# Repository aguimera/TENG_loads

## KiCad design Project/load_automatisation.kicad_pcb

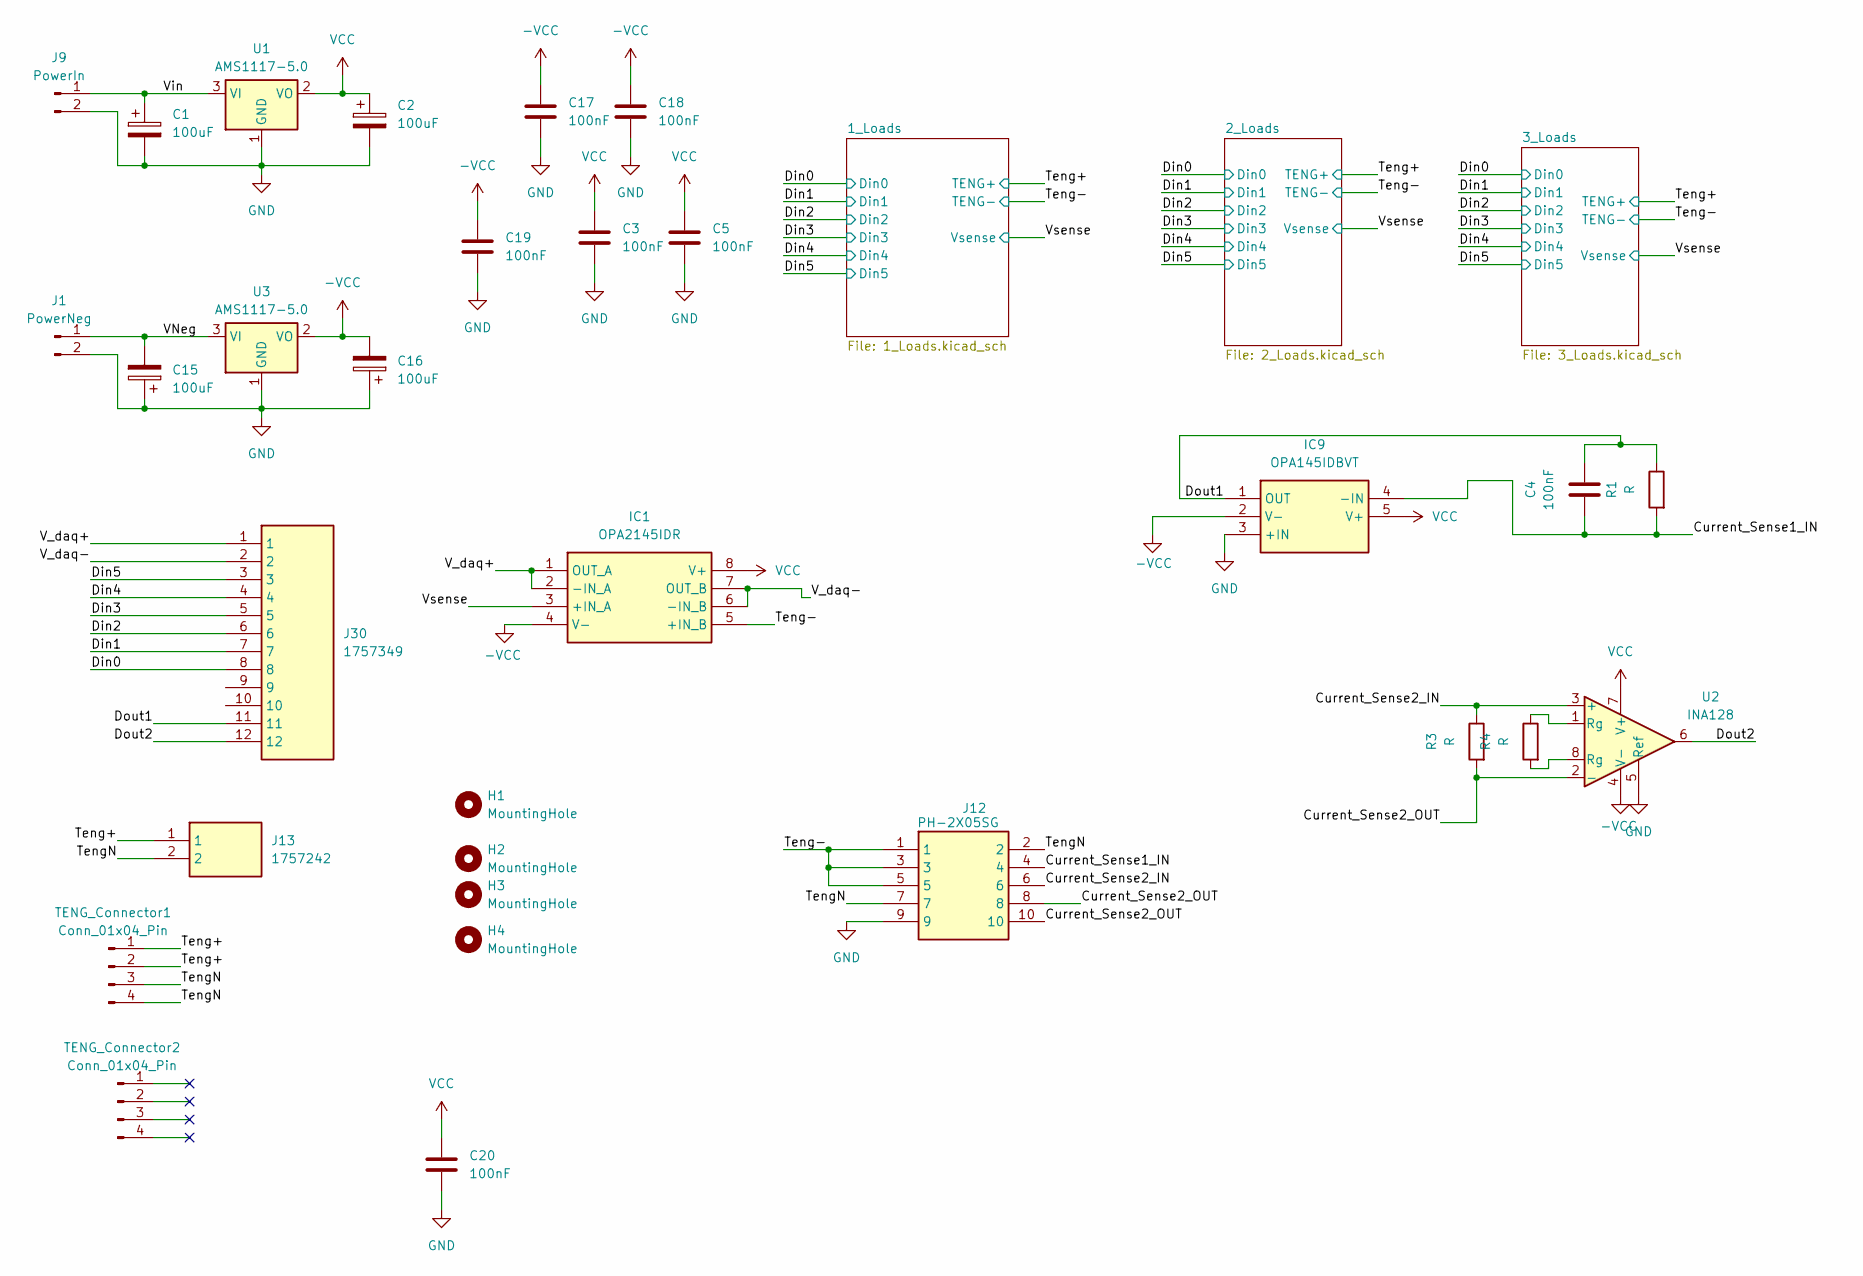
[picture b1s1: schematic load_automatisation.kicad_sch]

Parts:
C1, C2, C15, C16: 100uF; CP_Radial_D8.0mm_P3.80mm
C3, C4, C5, C17, C18, C19, C20: 100nF; C_0805_2012Metric
H1, H2, H3, H4: MountingHole; MountingHole_5.3mm_M5
IC1: OPA2145IDR; SOIC127P600X175-8N; Manufacturer_Part_Number OPA2145IDR; Mouser Part Number 595-OPA2145IDR
IC9: OPA145IDBVT; SOT95P280X145-5N; Manufacturer_Part_Number OPA145IDBVT; Mouser Part Number 595-OPA145IDBVT
J1: PowerNeg; PinHeader_1x02_P2.54mm_Vertical
J9: PowerIn; PinHeader_1x02_P2.54mm_Vertical
J12: PH-2X05SG; HDRV10W66P254_2X5_1270X500X895P; Manufacturer_Part_Number PH-2X05SG
J13: 1757242; Manufacturer_Part_Number 1757242; Mouser Part Number 651-1757242
J30: 1757349; SHDRRA12W103P0X508_1X12_6296X1200X875P; Manufacturer_Part_Number 1757349; Mouser Part Number 651-1757349
R1, R3, R4: R; R_0805_2012Metric
TENG_Connector1, TENG_Connector2: Conn_01x04_Pin; PinHeader_1x04_P2.54mm_Vertical
U1, U3: AMS1117-5.0; SOT-223-3_TabPin2
U2: INA128; SOIC-8_3.9x4.9mm_P1.27mm

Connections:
-VCC: C16.2, C17.1, C18.1, C19.1, IC1.4 (V-), IC9.2 (V-), U2.4 (V-), U3.2 (VO)
/Current_Sense1_IN: C4.1, IC9.4 (-IN), J12.4, R1.2
/Current_Sense2_IN: J12.6, R3.1, U2.3 (+)
/Current_Sense2_OUT: J12.8, J12.10, R3.2, U2.2 (-)
/Din0: J30.8; also elsewhere on the board
/Din1: J30.7; also elsewhere on the board
/Din2: J30.6; also elsewhere on the board
/Din3: J30.5; also elsewhere on the board
/Din4: J30.4; also elsewhere on the board
/Din5: J30.3; also elsewhere on the board
/Dout1: C4.2, IC9.1 (OUT), J30.11, R1.1
/Dout2: J30.12, U2.6
/Teng+: J13.1, TENG_Connector1.1, TENG_Connector1.2; also elsewhere on the board
/Teng-: IC1.5 (+IN_B), J12.1, J12.3, J12.5; also elsewhere on the board
/TengN: J12.2, J12.7, J13.2, TENG_Connector1.3, TENG_Connector1.4
/VNeg: C15.2, J1.1, U3.3 (VI)
/V_daq+: IC1.1 (OUT_A), IC1.2 (-IN_A), J30.1
/V_daq-: IC1.6 (-IN_B), IC1.7 (OUT_B), J30.2
/Vin: C1.1, J9.1, U1.3 (VI)
/Vsense: IC1.3 (+IN_A); also elsewhere on the board
GND: C1.2, C2.2, C3.2, C5.2, C15.1, C16.1, C17.2, C18.2, C19.2, C20.2, IC9.3 (+IN), J1.2, J9.2, J12.9, U1.1 (GND), U2.5 (Ref), U3.1 (GND); also elsewhere on the board
unnamed: R4.1, U2.1 (Rg)
unnamed: R4.2, U2.8 (Rg)
VCC: C2.1, C3.1, C5.1, C20.1, IC1.8 (V+), IC9.5 (V+), U1.2 (VO), U2.7 (V+); also elsewhere on the board

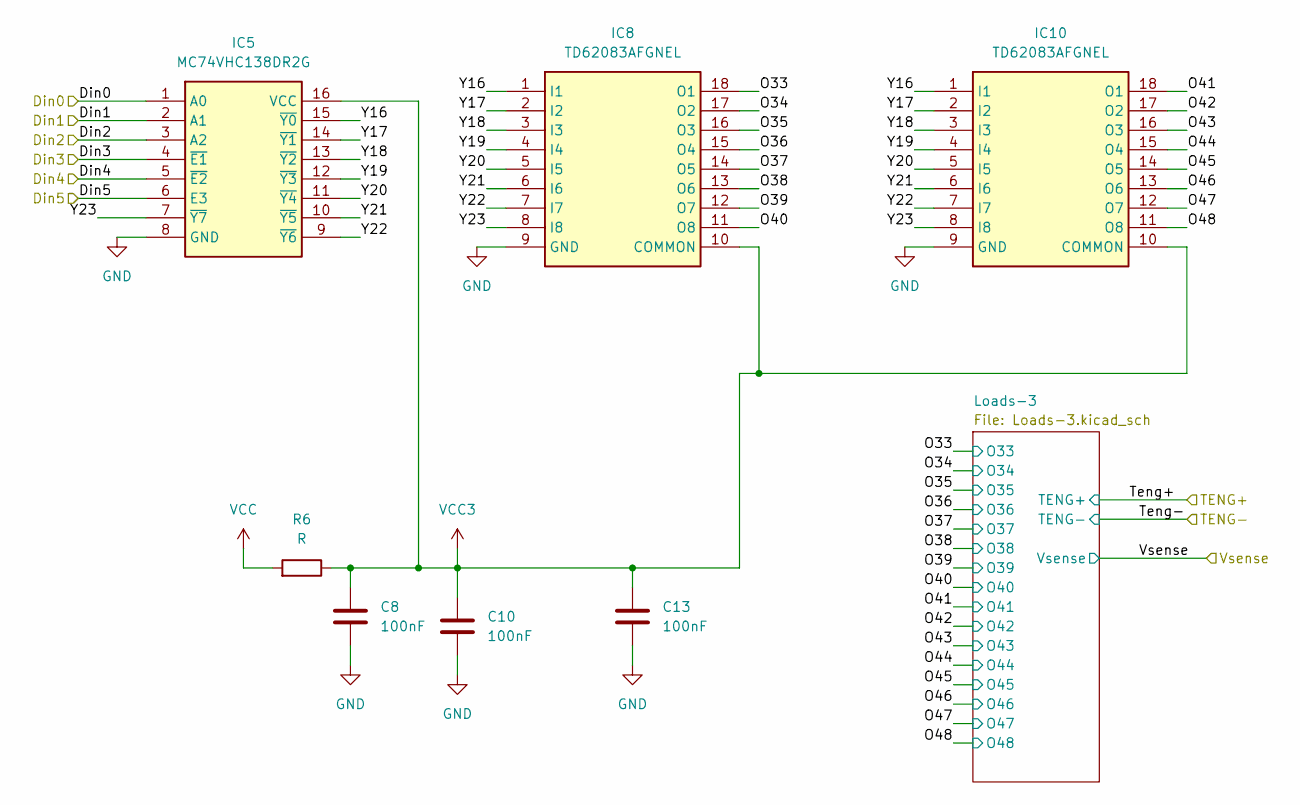
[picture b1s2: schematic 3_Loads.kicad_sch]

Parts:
C8, C10, C13: 100nF; C_0805_2012Metric
IC5: MC74VHC138DR2G; SOIC127P600X175-16N; Manufacturer_Part_Number MC74VHC138DR2G; Mouser Part Number 863-MC74VHC138DR2G
IC8, IC10: TD62083AFGNEL; SOIC127P1030X245-18N; Manufacturer_Part_Number TD62083AFGNEL; Mouser Part Number N/A
R6: R; R_0805_2012Metric

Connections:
/3_Loads/O33: IC8.18 (O1); also elsewhere on the board
/3_Loads/O34: IC8.17 (O2); also elsewhere on the board
/3_Loads/O35: IC8.16 (O3); also elsewhere on the board
/3_Loads/O36: IC8.15 (O4); also elsewhere on the board
/3_Loads/O37: IC8.14 (O5); also elsewhere on the board
/3_Loads/O38: IC8.13 (O6); also elsewhere on the board
/3_Loads/O39: IC8.12 (O7); also elsewhere on the board
/3_Loads/O40: IC8.11 (O8); also elsewhere on the board
/3_Loads/O41: IC10.18 (O1); also elsewhere on the board
/3_Loads/O42: IC10.17 (O2); also elsewhere on the board
/3_Loads/O43: IC10.16 (O3); also elsewhere on the board
/3_Loads/O44: IC10.15 (O4); also elsewhere on the board
/3_Loads/O45: IC10.14 (O5); also elsewhere on the board
/3_Loads/O46: IC10.13 (O6); also elsewhere on the board
/3_Loads/O47: IC10.12 (O7); also elsewhere on the board
/3_Loads/O48: IC10.11 (O8); also elsewhere on the board
/3_Loads/Y16: IC5.15 (~Y0), IC8.1 (I1), IC10.1 (I1)
/3_Loads/Y17: IC5.14 (~Y1), IC8.2 (I2), IC10.2 (I2)
/3_Loads/Y18: IC5.13 (~Y2), IC8.3 (I3), IC10.3 (I3)
/3_Loads/Y19: IC5.12 (~Y3), IC8.4 (I4), IC10.4 (I4)
/3_Loads/Y20: IC5.11 (~Y4), IC8.5 (I5), IC10.5 (I5)
/3_Loads/Y21: IC5.10 (~Y5), IC8.6 (I6), IC10.6 (I6)
/3_Loads/Y22: IC5.9 (~Y6), IC8.7 (I7), IC10.7 (I7)
/3_Loads/Y23: IC5.7 (~Y7), IC8.8 (I8), IC10.8 (I8)
/Din0: IC5.1 (A0); also elsewhere on the board
/Din1: IC5.2 (A1); also elsewhere on the board
/Din2: IC5.3 (A2); also elsewhere on the board
/Din3: IC5.4 (~E1); also elsewhere on the board
/Din4: IC5.5 (~E2); also elsewhere on the board
/Din5: IC5.6 (E3); also elsewhere on the board
GND: C8.2, C10.2, C13.2, IC5.8 (GND), IC8.9 (GND), IC10.9 (GND); also elsewhere on the board
VCC: R6.2; also elsewhere on the board
VCC3: C8.1, C10.1, C13.1, IC5.16 (VCC), IC8.10 (COMMON), IC10.10 (COMMON), R6.1

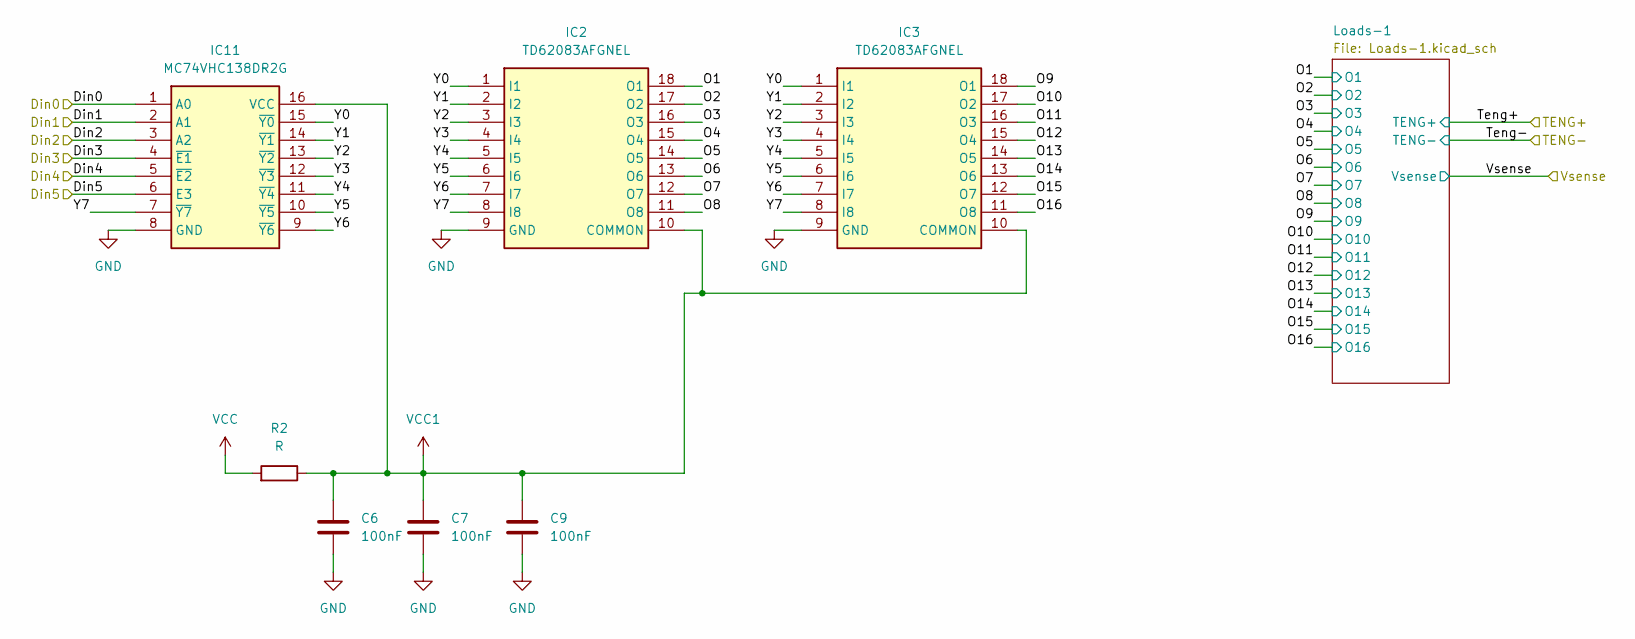
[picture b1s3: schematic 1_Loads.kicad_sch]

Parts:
C6, C7, C9: 100nF; C_0805_2012Metric
IC2, IC3: TD62083AFGNEL; SOIC127P1030X245-18N; Manufacturer_Part_Number TD62083AFGNEL; Mouser Part Number N/A
IC11: MC74VHC138DR2G; SOIC127P600X175-16N; Manufacturer_Part_Number MC74VHC138DR2G; Mouser Part Number 863-MC74VHC138DR2G
R2: R; R_0805_2012Metric

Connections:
/1_Loads/O1: IC2.18 (O1); also elsewhere on the board
/1_Loads/O2: IC2.17 (O2); also elsewhere on the board
/1_Loads/O3: IC2.16 (O3); also elsewhere on the board
/1_Loads/O4: IC2.15 (O4); also elsewhere on the board
/1_Loads/O5: IC2.14 (O5); also elsewhere on the board
/1_Loads/O6: IC2.13 (O6); also elsewhere on the board
/1_Loads/O7: IC2.12 (O7); also elsewhere on the board
/1_Loads/O8: IC2.11 (O8); also elsewhere on the board
/1_Loads/O9: IC3.18 (O1); also elsewhere on the board
/1_Loads/O10: IC3.17 (O2); also elsewhere on the board
/1_Loads/O11: IC3.16 (O3); also elsewhere on the board
/1_Loads/O12: IC3.15 (O4); also elsewhere on the board
/1_Loads/O13: IC3.14 (O5); also elsewhere on the board
/1_Loads/O14: IC3.13 (O6); also elsewhere on the board
/1_Loads/O15: IC3.12 (O7); also elsewhere on the board
/1_Loads/O16: IC3.11 (O8); also elsewhere on the board
/1_Loads/Y0: IC2.1 (I1), IC3.1 (I1), IC11.15 (~Y0)
/1_Loads/Y1: IC2.2 (I2), IC3.2 (I2), IC11.14 (~Y1)
/1_Loads/Y2: IC2.3 (I3), IC3.3 (I3), IC11.13 (~Y2)
/1_Loads/Y3: IC2.4 (I4), IC3.4 (I4), IC11.12 (~Y3)
/1_Loads/Y4: IC2.5 (I5), IC3.5 (I5), IC11.11 (~Y4)
/1_Loads/Y5: IC2.6 (I6), IC3.6 (I6), IC11.10 (~Y5)
/1_Loads/Y6: IC2.7 (I7), IC3.7 (I7), IC11.9 (~Y6)
/1_Loads/Y7: IC2.8 (I8), IC3.8 (I8), IC11.7 (~Y7)
/Din0: IC11.1 (A0); also elsewhere on the board
/Din1: IC11.2 (A1); also elsewhere on the board
/Din2: IC11.3 (A2); also elsewhere on the board
/Din3: IC11.4 (~E1); also elsewhere on the board
/Din4: IC11.5 (~E2); also elsewhere on the board
/Din5: IC11.6 (E3); also elsewhere on the board
GND: C6.2, C7.2, C9.2, IC2.9 (GND), IC3.9 (GND), IC11.8 (GND); also elsewhere on the board
VCC: R2.2; also elsewhere on the board
VCC1: C6.1, C7.1, C9.1, IC2.10 (COMMON), IC3.10 (COMMON), IC11.16 (VCC), R2.1

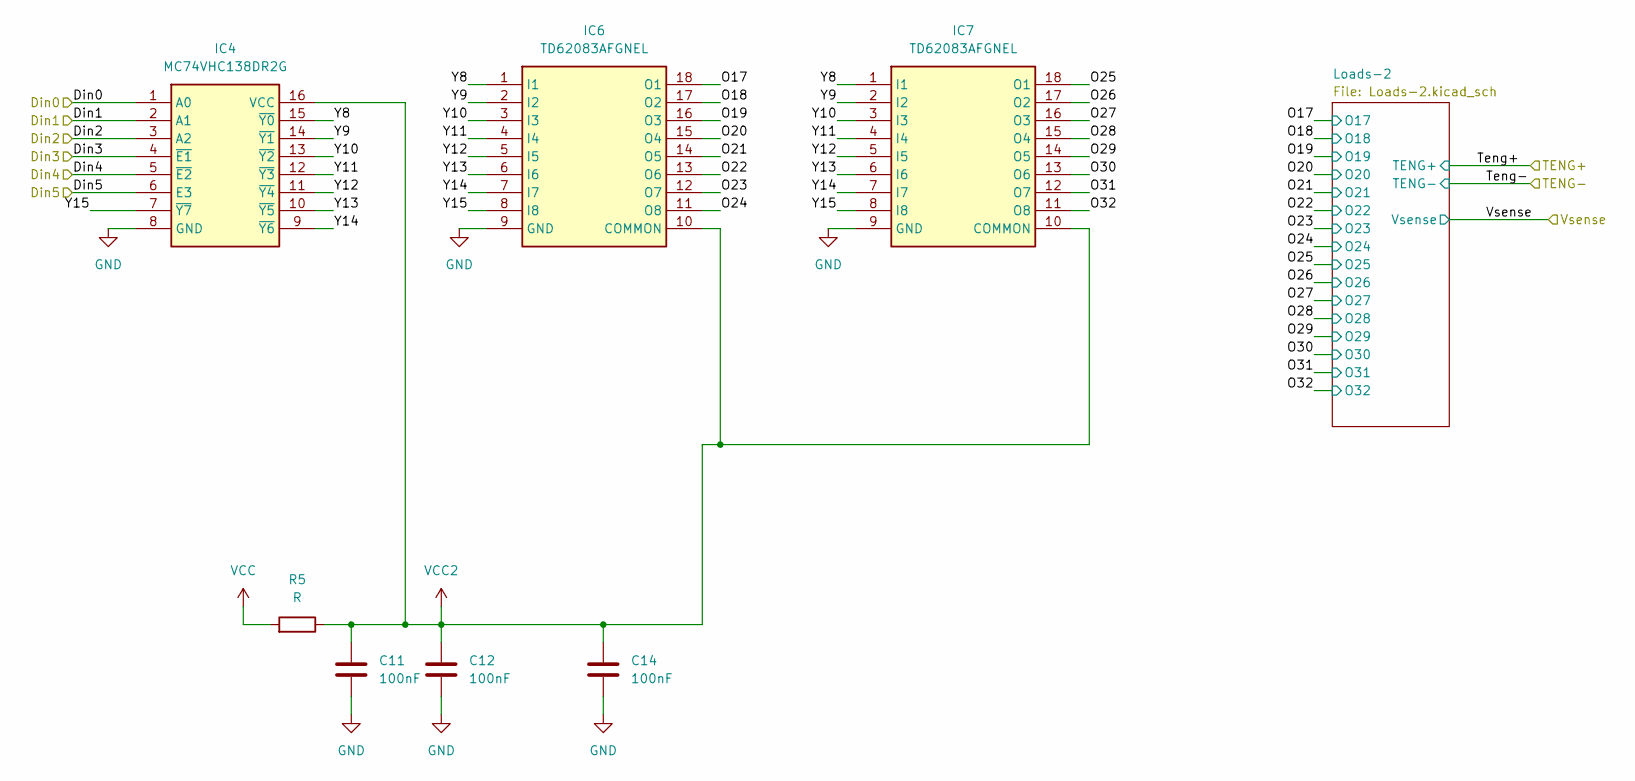
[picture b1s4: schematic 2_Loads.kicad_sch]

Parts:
C11, C12, C14: 100nF; C_0805_2012Metric
IC4: MC74VHC138DR2G; SOIC127P600X175-16N; Manufacturer_Part_Number MC74VHC138DR2G; Mouser Part Number 863-MC74VHC138DR2G
IC6, IC7: TD62083AFGNEL; SOIC127P1030X245-18N; Manufacturer_Part_Number TD62083AFGNEL; Mouser Part Number N/A
R5: R; R_0805_2012Metric

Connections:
/2_Loads/O17: IC6.18 (O1); also elsewhere on the board
/2_Loads/O18: IC6.17 (O2); also elsewhere on the board
/2_Loads/O19: IC6.16 (O3); also elsewhere on the board
/2_Loads/O20: IC6.15 (O4); also elsewhere on the board
/2_Loads/O21: IC6.14 (O5); also elsewhere on the board
/2_Loads/O22: IC6.13 (O6); also elsewhere on the board
/2_Loads/O23: IC6.12 (O7); also elsewhere on the board
/2_Loads/O24: IC6.11 (O8); also elsewhere on the board
/2_Loads/O25: IC7.18 (O1); also elsewhere on the board
/2_Loads/O26: IC7.17 (O2); also elsewhere on the board
/2_Loads/O27: IC7.16 (O3); also elsewhere on the board
/2_Loads/O28: IC7.15 (O4); also elsewhere on the board
/2_Loads/O29: IC7.14 (O5); also elsewhere on the board
/2_Loads/O30: IC7.13 (O6); also elsewhere on the board
/2_Loads/O31: IC7.12 (O7); also elsewhere on the board
/2_Loads/O32: IC7.11 (O8); also elsewhere on the board
/2_Loads/Y8: IC4.15 (~Y0), IC6.1 (I1), IC7.1 (I1)
/2_Loads/Y9: IC4.14 (~Y1), IC6.2 (I2), IC7.2 (I2)
/2_Loads/Y10: IC4.13 (~Y2), IC6.3 (I3), IC7.3 (I3)
/2_Loads/Y11: IC4.12 (~Y3), IC6.4 (I4), IC7.4 (I4)
/2_Loads/Y12: IC4.11 (~Y4), IC6.5 (I5), IC7.5 (I5)
/2_Loads/Y13: IC4.10 (~Y5), IC6.6 (I6), IC7.6 (I6)
/2_Loads/Y14: IC4.9 (~Y6), IC6.7 (I7), IC7.7 (I7)
/2_Loads/Y15: IC4.7 (~Y7), IC6.8 (I8), IC7.8 (I8)
/Din0: IC4.1 (A0); also elsewhere on the board
/Din1: IC4.2 (A1); also elsewhere on the board
/Din2: IC4.3 (A2); also elsewhere on the board
/Din3: IC4.4 (~E1); also elsewhere on the board
/Din4: IC4.5 (~E2); also elsewhere on the board
/Din5: IC4.6 (E3); also elsewhere on the board
GND: C11.2, C12.2, C14.2, IC4.8 (GND), IC6.9 (GND), IC7.9 (GND); also elsewhere on the board
VCC: R5.2; also elsewhere on the board
VCC2: C11.1, C12.1, C14.1, IC4.16 (VCC), IC6.10 (COMMON), IC7.10 (COMMON), R5.1

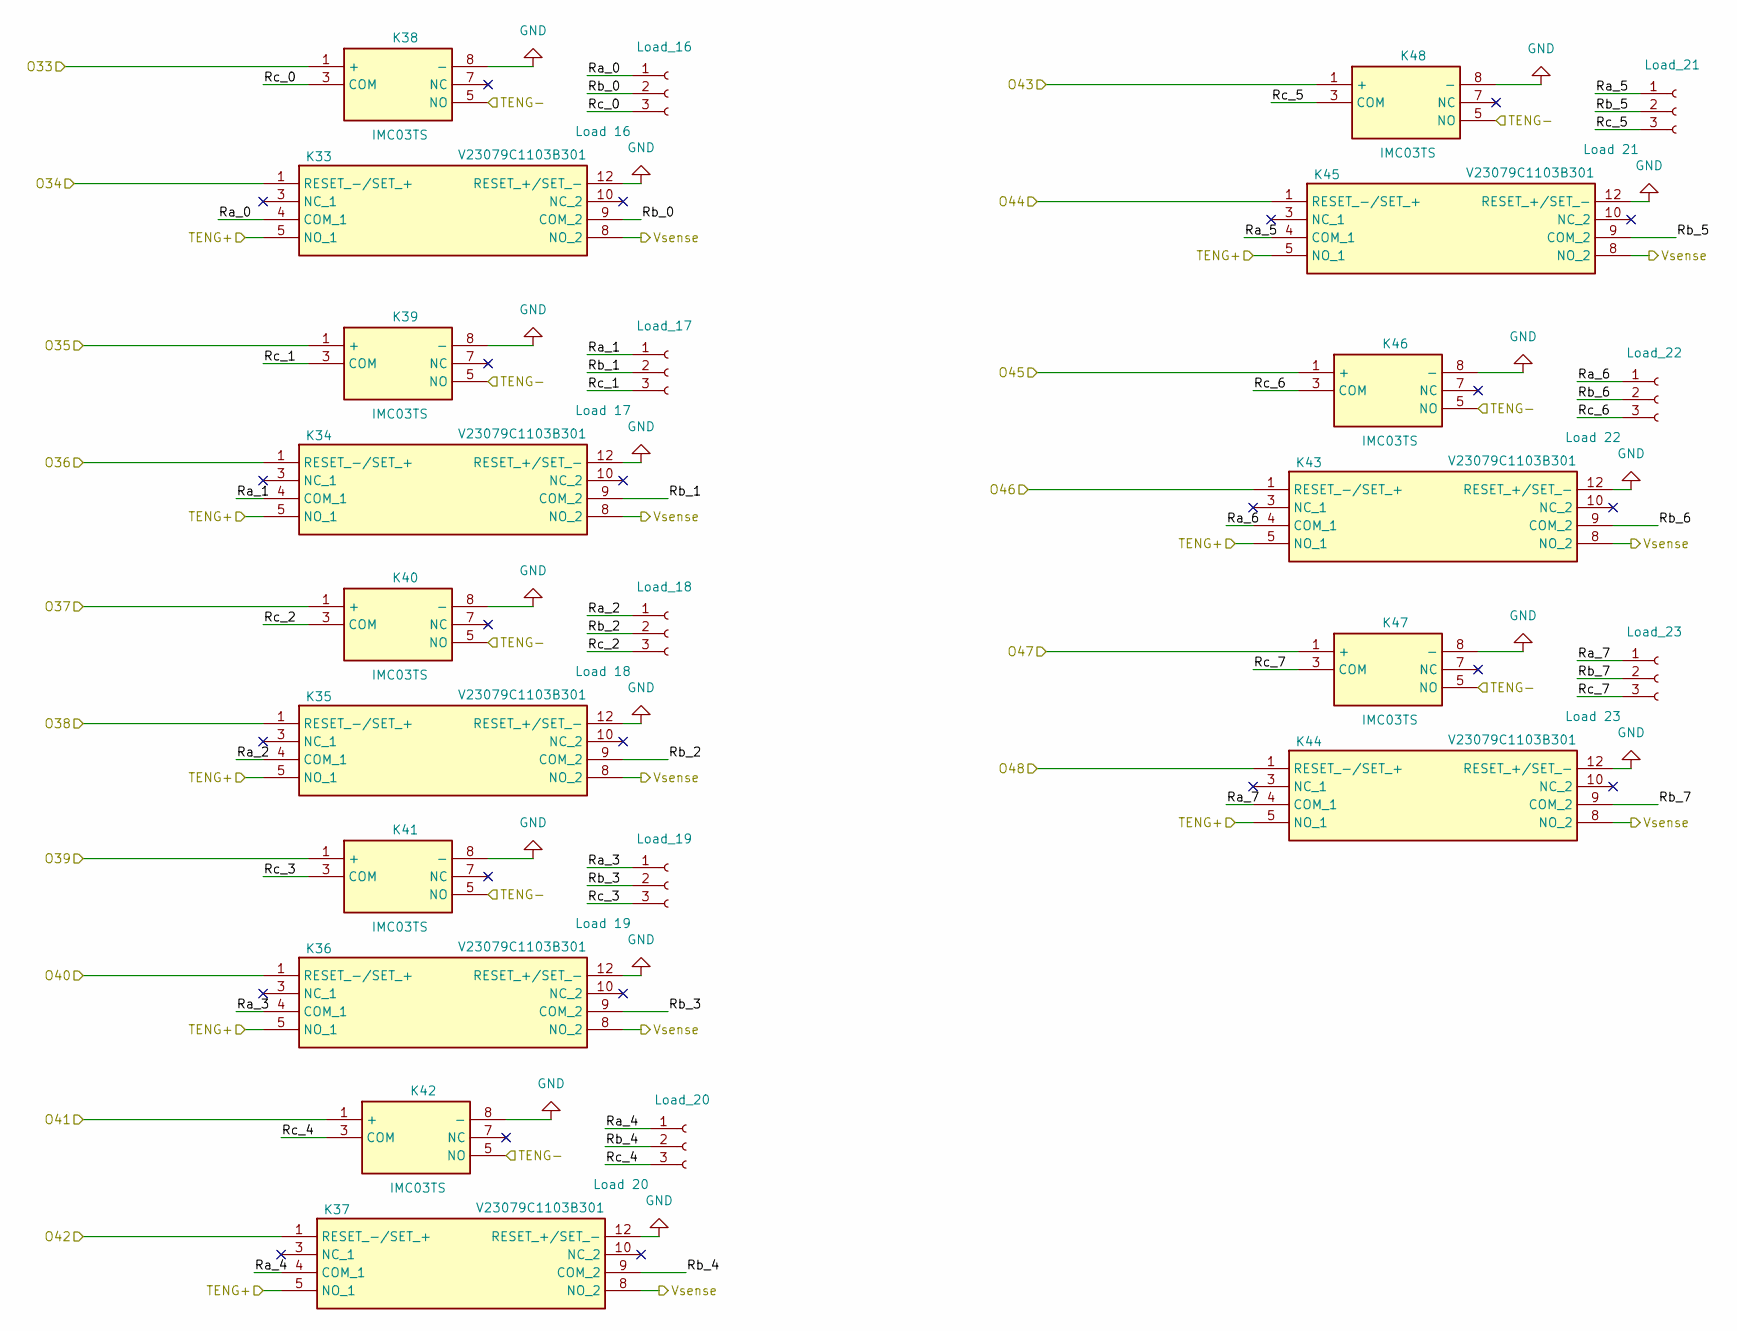
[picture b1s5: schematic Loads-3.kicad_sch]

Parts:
K33, K34, K35, K36, K37, K43, K44, K45: V23079C1103B301; V23079A1001B301; Manufacturer_Part_Number V23079C1103B301; Mouser Part Number 655-V23079C1103B301
K38, K39, K40, K41, K42, K46, K47, K48: IMC03TS; Manufacturer_Part_Number IMC03TS; Mouser Part Number 655-IMC03TS
Load_16: Load 16; PinHeader_1x03_P2.54mm_Vertical
Load_17: Load 17; PinHeader_1x03_P2.54mm_Vertical
Load_18: Load 18; PinHeader_1x03_P2.54mm_Vertical
Load_19: Load 19; PinHeader_1x03_P2.54mm_Vertical
Load_20: Load 20; PinHeader_1x03_P2.54mm_Vertical
Load_21: Load 21; PinHeader_1x03_P2.54mm_Vertical
Load_22: Load 22; PinHeader_1x03_P2.54mm_Vertical
Load_23: Load 23; PinHeader_1x03_P2.54mm_Vertical

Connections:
/3_Loads/Loads-3/Ra_0: K33.4 (COM_1), Load_16.1
/3_Loads/Loads-3/Ra_1: K34.4 (COM_1), Load_17.1
/3_Loads/Loads-3/Ra_2: K35.4 (COM_1), Load_18.1
/3_Loads/Loads-3/Ra_3: K36.4 (COM_1), Load_19.1
/3_Loads/Loads-3/Ra_4: K37.4 (COM_1), Load_20.1
/3_Loads/Loads-3/Ra_5: K45.4 (COM_1), Load_21.1
/3_Loads/Loads-3/Ra_6: K43.4 (COM_1), Load_22.1
/3_Loads/Loads-3/Ra_7: K44.4 (COM_1), Load_23.1
/3_Loads/Loads-3/Rb_0: K33.9 (COM_2), Load_16.2
/3_Loads/Loads-3/Rb_1: K34.9 (COM_2), Load_17.2
/3_Loads/Loads-3/Rb_2: K35.9 (COM_2), Load_18.2
/3_Loads/Loads-3/Rb_3: K36.9 (COM_2), Load_19.2
/3_Loads/Loads-3/Rb_4: K37.9 (COM_2), Load_20.2
/3_Loads/Loads-3/Rb_5: K45.9 (COM_2), Load_21.2
/3_Loads/Loads-3/Rb_6: K43.9 (COM_2), Load_22.2
/3_Loads/Loads-3/Rb_7: K44.9 (COM_2), Load_23.2
/3_Loads/Loads-3/Rc_0: K38.3 (COM), Load_16.3
/3_Loads/Loads-3/Rc_1: K39.3 (COM), Load_17.3
/3_Loads/Loads-3/Rc_2: K40.3 (COM), Load_18.3
/3_Loads/Loads-3/Rc_3: K41.3 (COM), Load_19.3
/3_Loads/Loads-3/Rc_4: K42.3 (COM), Load_20.3
/3_Loads/Loads-3/Rc_5: K48.3 (COM), Load_21.3
/3_Loads/Loads-3/Rc_6: K46.3 (COM), Load_22.3
/3_Loads/Loads-3/Rc_7: K47.3 (COM), Load_23.3
/3_Loads/O33: K38.1 (+); also elsewhere on the board
/3_Loads/O34: K33.1 (RESET_-/SET_+); also elsewhere on the board
/3_Loads/O35: K39.1 (+); also elsewhere on the board
/3_Loads/O36: K34.1 (RESET_-/SET_+); also elsewhere on the board
/3_Loads/O37: K40.1 (+); also elsewhere on the board
/3_Loads/O38: K35.1 (RESET_-/SET_+); also elsewhere on the board
/3_Loads/O39: K41.1 (+); also elsewhere on the board
/3_Loads/O40: K36.1 (RESET_-/SET_+); also elsewhere on the board
/3_Loads/O41: K42.1 (+); also elsewhere on the board
/3_Loads/O42: K37.1 (RESET_-/SET_+); also elsewhere on the board
/3_Loads/O43: K48.1 (+); also elsewhere on the board
/3_Loads/O44: K45.1 (RESET_-/SET_+); also elsewhere on the board
/3_Loads/O45: K46.1 (+); also elsewhere on the board
/3_Loads/O46: K43.1 (RESET_-/SET_+); also elsewhere on the board
/3_Loads/O47: K47.1 (+); also elsewhere on the board
/3_Loads/O48: K44.1 (RESET_-/SET_+); also elsewhere on the board
/Teng+: K33.5 (NO_1), K34.5 (NO_1), K35.5 (NO_1), K36.5 (NO_1), K37.5 (NO_1), K43.5 (NO_1), K44.5 (NO_1), K45.5 (NO_1); also elsewhere on the board
/Teng-: K38.5 (NO), K39.5 (NO), K40.5 (NO), K41.5 (NO), K42.5 (NO), K46.5 (NO), K47.5 (NO), K48.5 (NO); also elsewhere on the board
/Vsense: K33.8 (NO_2), K34.8 (NO_2), K35.8 (NO_2), K36.8 (NO_2), K37.8 (NO_2), K43.8 (NO_2), K44.8 (NO_2), K45.8 (NO_2); also elsewhere on the board
GND: K33.12 (RESET_+/SET_-), K34.12 (RESET_+/SET_-), K35.12 (RESET_+/SET_-), K36.12 (RESET_+/SET_-), K37.12 (RESET_+/SET_-), K38.8 (-), K39.8 (-), K40.8 (-), K41.8 (-), K42.8 (-), K43.12 (RESET_+/SET_-), K44.12 (RESET_+/SET_-), K45.12 (RESET_+/SET_-), K46.8 (-), K47.8 (-), K48.8 (-); also elsewhere on the board

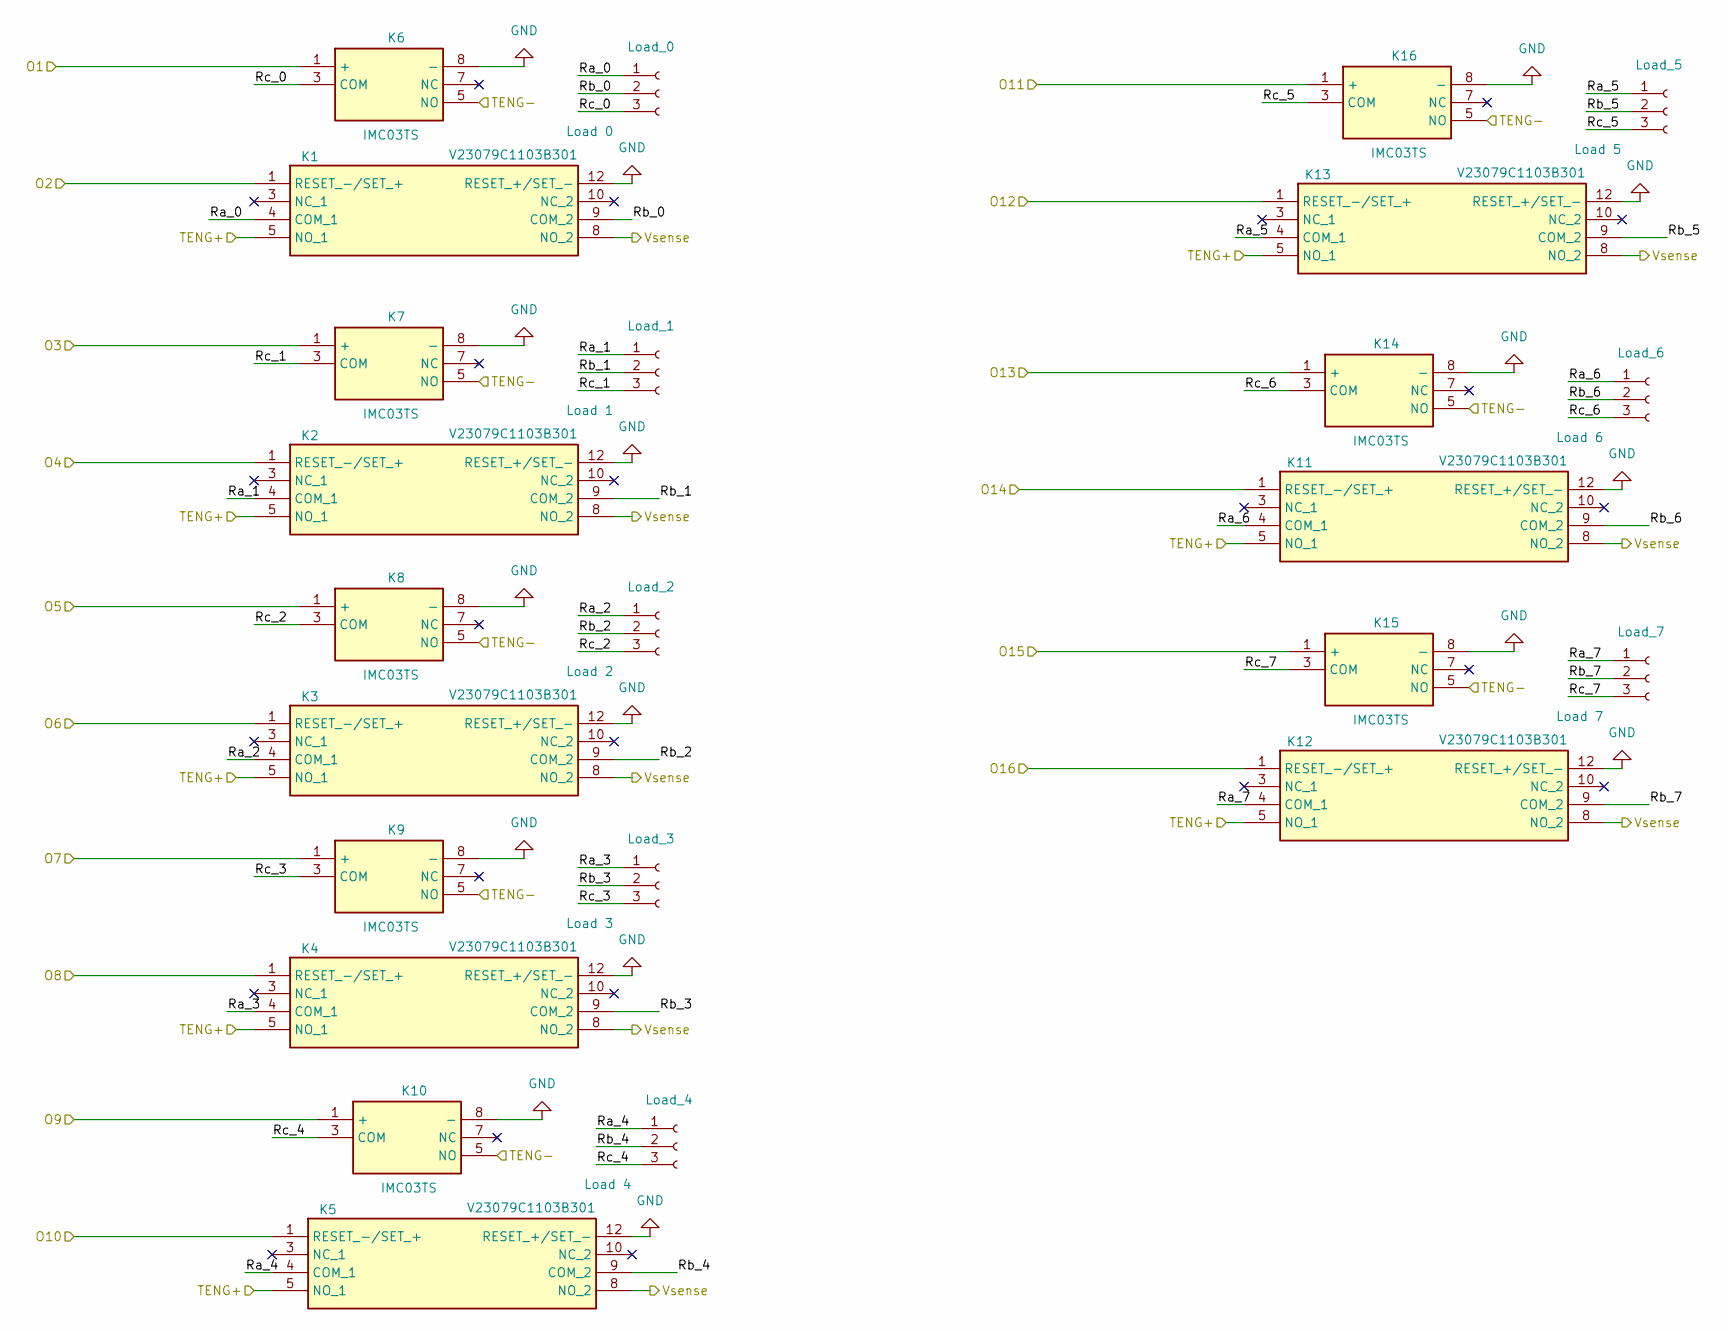
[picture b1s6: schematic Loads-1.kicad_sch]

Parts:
K1, K2, K3, K4, K5, K11, K12, K13: V23079C1103B301; V23079A1001B301; Manufacturer_Part_Number V23079C1103B301; Mouser Part Number 655-V23079C1103B301
K6, K7, K8, K9, K10, K14, K15, K16: IMC03TS; Manufacturer_Part_Number IMC03TS; Mouser Part Number 655-IMC03TS
Load_0: Load 0; PinHeader_1x03_P2.54mm_Vertical
Load_1: Load 1; PinHeader_1x03_P2.54mm_Vertical
Load_2: Load 2; PinHeader_1x03_P2.54mm_Vertical
Load_3: Load 3; PinHeader_1x03_P2.54mm_Vertical
Load_4: Load 4; PinHeader_1x03_P2.54mm_Vertical
Load_5: Load 5; PinHeader_1x03_P2.54mm_Vertical
Load_6: Load 6; PinHeader_1x03_P2.54mm_Vertical
Load_7: Load 7; PinHeader_1x03_P2.54mm_Vertical

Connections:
/1_Loads/Loads-1/Ra_0: K1.4 (COM_1), Load_0.1
/1_Loads/Loads-1/Ra_1: K2.4 (COM_1), Load_1.1
/1_Loads/Loads-1/Ra_2: K3.4 (COM_1), Load_2.1
/1_Loads/Loads-1/Ra_3: K4.4 (COM_1), Load_3.1
/1_Loads/Loads-1/Ra_4: K5.4 (COM_1), Load_4.1
/1_Loads/Loads-1/Ra_5: K13.4 (COM_1), Load_5.1
/1_Loads/Loads-1/Ra_6: K11.4 (COM_1), Load_6.1
/1_Loads/Loads-1/Ra_7: K12.4 (COM_1), Load_7.1
/1_Loads/Loads-1/Rb_0: K1.9 (COM_2), Load_0.2
/1_Loads/Loads-1/Rb_1: K2.9 (COM_2), Load_1.2
/1_Loads/Loads-1/Rb_2: K3.9 (COM_2), Load_2.2
/1_Loads/Loads-1/Rb_3: K4.9 (COM_2), Load_3.2
/1_Loads/Loads-1/Rb_4: K5.9 (COM_2), Load_4.2
/1_Loads/Loads-1/Rb_5: K13.9 (COM_2), Load_5.2
/1_Loads/Loads-1/Rb_6: K11.9 (COM_2), Load_6.2
/1_Loads/Loads-1/Rb_7: K12.9 (COM_2), Load_7.2
/1_Loads/Loads-1/Rc_0: K6.3 (COM), Load_0.3
/1_Loads/Loads-1/Rc_1: K7.3 (COM), Load_1.3
/1_Loads/Loads-1/Rc_2: K8.3 (COM), Load_2.3
/1_Loads/Loads-1/Rc_3: K9.3 (COM), Load_3.3
/1_Loads/Loads-1/Rc_4: K10.3 (COM), Load_4.3
/1_Loads/Loads-1/Rc_5: K16.3 (COM), Load_5.3
/1_Loads/Loads-1/Rc_6: K14.3 (COM), Load_6.3
/1_Loads/Loads-1/Rc_7: K15.3 (COM), Load_7.3
/1_Loads/O1: K6.1 (+); also elsewhere on the board
/1_Loads/O2: K1.1 (RESET_-/SET_+); also elsewhere on the board
/1_Loads/O3: K7.1 (+); also elsewhere on the board
/1_Loads/O4: K2.1 (RESET_-/SET_+); also elsewhere on the board
/1_Loads/O5: K8.1 (+); also elsewhere on the board
/1_Loads/O6: K3.1 (RESET_-/SET_+); also elsewhere on the board
/1_Loads/O7: K9.1 (+); also elsewhere on the board
/1_Loads/O8: K4.1 (RESET_-/SET_+); also elsewhere on the board
/1_Loads/O9: K10.1 (+); also elsewhere on the board
/1_Loads/O10: K5.1 (RESET_-/SET_+); also elsewhere on the board
/1_Loads/O11: K16.1 (+); also elsewhere on the board
/1_Loads/O12: K13.1 (RESET_-/SET_+); also elsewhere on the board
/1_Loads/O13: K14.1 (+); also elsewhere on the board
/1_Loads/O14: K11.1 (RESET_-/SET_+); also elsewhere on the board
/1_Loads/O15: K15.1 (+); also elsewhere on the board
/1_Loads/O16: K12.1 (RESET_-/SET_+); also elsewhere on the board
/Teng+: K1.5 (NO_1), K2.5 (NO_1), K3.5 (NO_1), K4.5 (NO_1), K5.5 (NO_1), K11.5 (NO_1), K12.5 (NO_1), K13.5 (NO_1); also elsewhere on the board
/Teng-: K6.5 (NO), K7.5 (NO), K8.5 (NO), K9.5 (NO), K10.5 (NO), K14.5 (NO), K15.5 (NO), K16.5 (NO); also elsewhere on the board
/Vsense: K1.8 (NO_2), K2.8 (NO_2), K3.8 (NO_2), K4.8 (NO_2), K5.8 (NO_2), K11.8 (NO_2), K12.8 (NO_2), K13.8 (NO_2); also elsewhere on the board
GND: K1.12 (RESET_+/SET_-), K2.12 (RESET_+/SET_-), K3.12 (RESET_+/SET_-), K4.12 (RESET_+/SET_-), K5.12 (RESET_+/SET_-), K6.8 (-), K7.8 (-), K8.8 (-), K9.8 (-), K10.8 (-), K11.12 (RESET_+/SET_-), K12.12 (RESET_+/SET_-), K13.12 (RESET_+/SET_-), K14.8 (-), K15.8 (-), K16.8 (-); also elsewhere on the board
